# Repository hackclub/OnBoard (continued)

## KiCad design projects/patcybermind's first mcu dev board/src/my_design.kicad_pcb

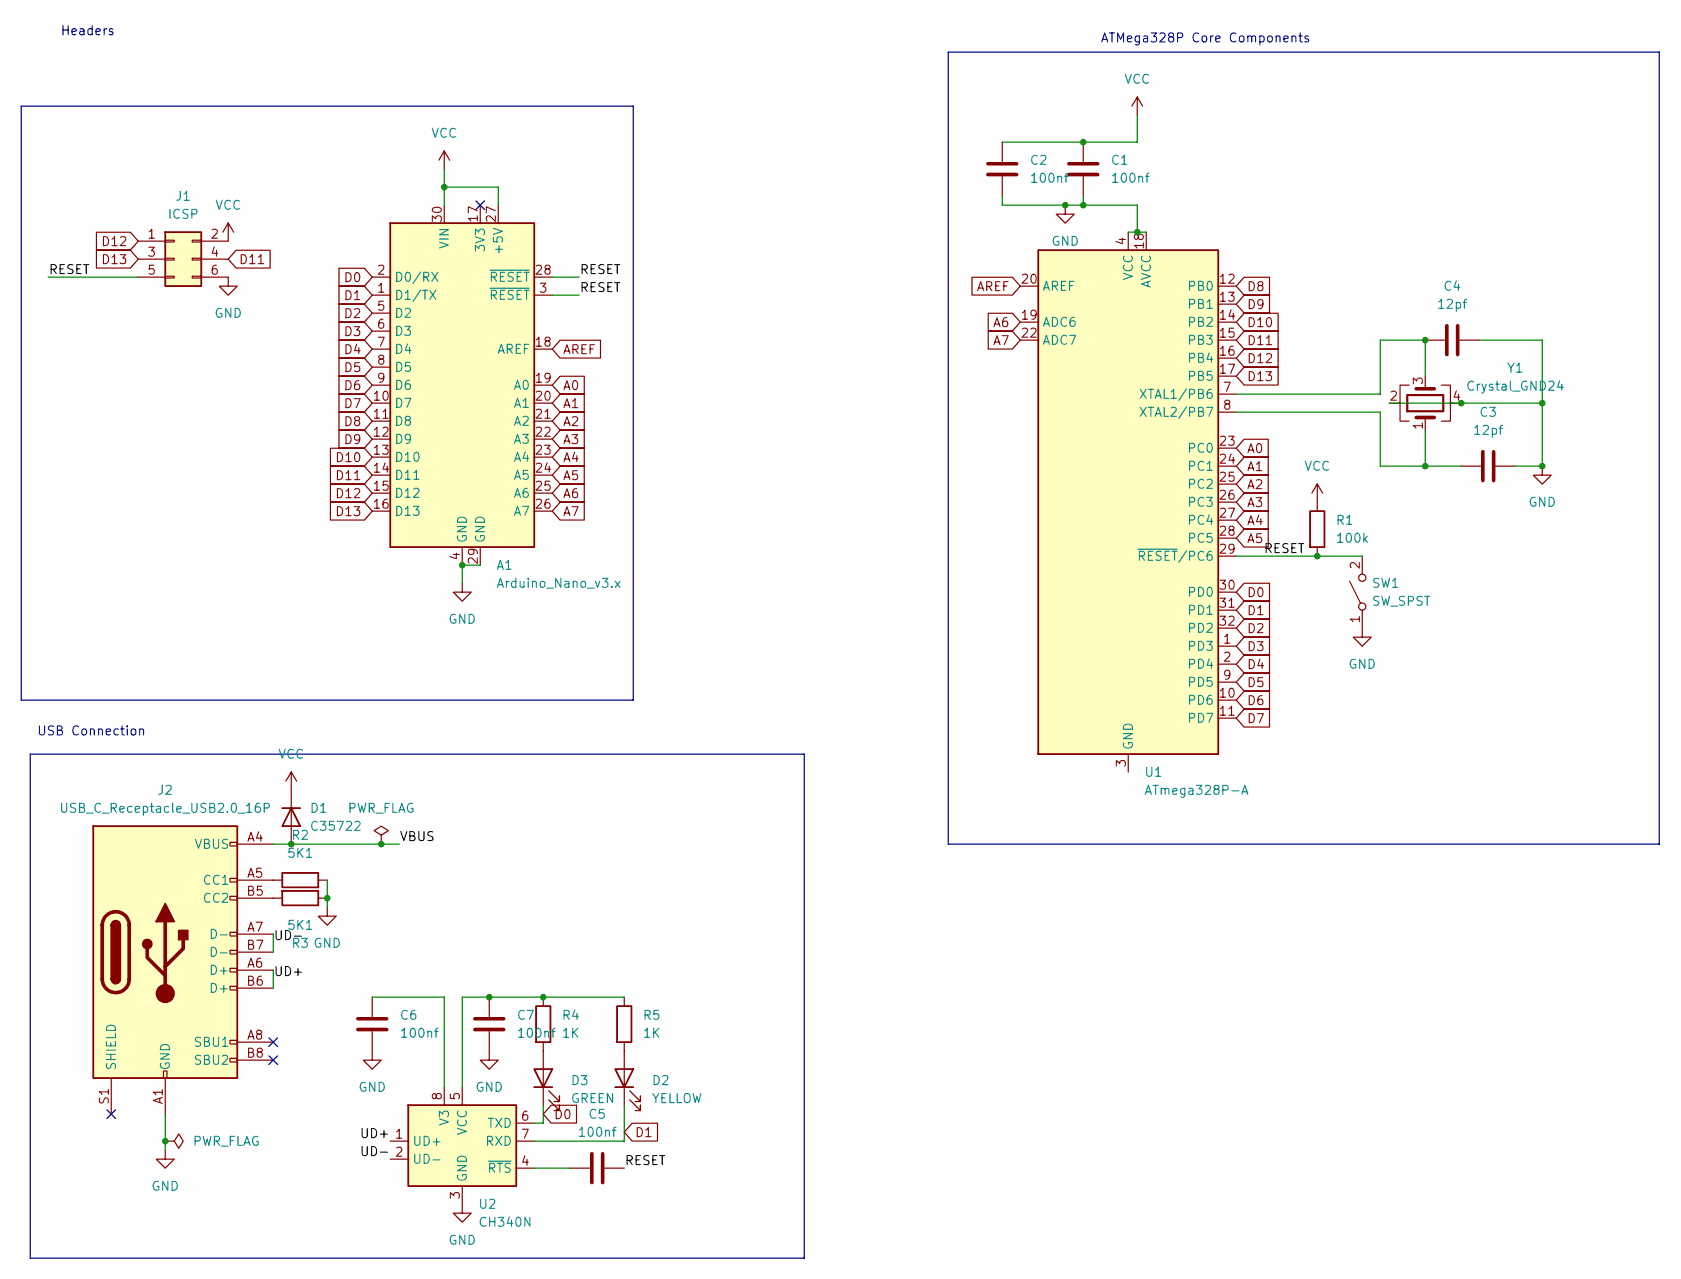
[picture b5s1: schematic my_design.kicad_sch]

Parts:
A1: Arduino_Nano_v3.x; Arduino_Nano_WithMountingHoles
C1, C2, C5, C6, C7: 100nf; C_0805_2012Metric_Pad1.18x1.45mm_HandSolder; LCSC C49678
C3, C4: 12pf; C_0805_2012Metric_Pad1.18x1.45mm_HandSolder; LCSC C1792
D1: C35722; D_SMC_Handsoldering; LCSC C35722
D2: YELLOW; LED_0805_2012Metric_Pad1.15x1.40mm_HandSolder; LCSC C2296
D3: GREEN; LED_0805_2012Metric_Pad1.15x1.40mm_HandSolder; LCSC C2297
J1: ICSP; PinHeader_2x03_P2.54mm_Vertical
J2: USB_C_Receptacle_USB2.0_16P; USB_C_Receptacle_HRO_TYPE-C-31-M-12; LCSC C2988369
R1: 100k; R_0805_2012Metric_Pad1.20x1.40mm_HandSolder; LCSC C17414
R2, R3: 5K1; R_0805_2012Metric_Pad1.20x1.40mm_HandSolder; LCSC C27834
R4, R5: 1K; R_0805_2012Metric_Pad1.20x1.40mm_HandSolder; LCSC C17513
SW1: SW_SPST; SW_Push_1P1T_XKB_TS-1187A; LCSC C318884
U1: ATmega328P-A; TQFP-32_7x7mm_P0.8mm; LCSC C14877
U2: CH340N; SOP-8_3.9x4.9mm_P1.27mm; LCSC C2977777
Y1: Crystal_GND24; Crystal_SMD_3225-4Pin_3.2x2.5mm_HandSoldering; LCSC C13738

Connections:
/RESET: A1.3 (~RESET), A1.28 (~RESET), C5.2, J1.5, R1.2, SW1.2 (B), U1.29 (~RESET/PC6)
/UD+: J2.A6 (D+), J2.B6 (D+), U2.1 (UD+)
/UD-: J2.A7 (D-), J2.B7 (D-), U2.2 (UD-)
/VBUS: D1.2 (A), J2.A4 (VBUS), J2.A9 (VBUS), J2.B4 (VBUS), J2.B9 (VBUS)
A0: A1.19 (A0), U1.23 (PC0)
A1: A1.20 (A1), U1.24 (PC1)
A2: A1.21 (A2), U1.25 (PC2)
A3: A1.22 (A3), U1.26 (PC3)
A4: A1.23 (A4), U1.27 (PC4)
A5: A1.24 (A5), U1.28 (PC5)
A6: A1.25 (A6), U1.19 (ADC6)
A7: A1.26 (A7), U1.22 (ADC7)
AREF: A1.18 (AREF), U1.20 (AREF)
D0: A1.2 (D0/RX), D3.1 (K), U1.30 (PD0), U2.6 (TXD)
D1: A1.1 (D1/TX), D2.1 (K), U1.31 (PD1), U2.7 (RXD)
D2: A1.5 (D2), U1.32 (PD2)
D3: A1.6 (D3), U1.1 (PD3)
D4: A1.7 (D4), U1.2 (PD4)
D5: A1.8 (D5), U1.9 (PD5)
D6: A1.9 (D6), U1.10 (PD6)
D7: A1.10 (D7), U1.11 (PD7)
D8: A1.11 (D8), U1.12 (PB0)
D9: A1.12 (D9), U1.13 (PB1)
D10: A1.13 (D10), U1.14 (PB2)
D11: A1.14 (D11), J1.4, U1.15 (PB3)
D12: A1.15 (D12), J1.1, U1.16 (PB4)
D13: A1.16 (D13), J1.3, U1.17 (PB5)
GND: A1.4 (GND), A1.29 (GND), C1.2, C2.1, C3.2, C4.2, C6.2, C7.2, J1.6, J2.A1 (GND), J2.A12 (GND), J2.B1 (GND), J2.B12 (GND), R2.2, R3.1, SW1.1 (A), U1.4 (VCC), U1.6 (VCC), U1.18 (AVCC), U2.3 (GND), Y1.2, Y1.4
unnamed: D2.2 (A), R5.2
unnamed: D3.2 (A), R4.2
unnamed: J2.A5 (CC1), R2.1
unnamed: J2.B5 (CC2), R3.2
unnamed: U1.3 (GND), U1.5 (GND), U1.21 (GND)
unnamed: C4.1, U1.7 (XTAL1/PB6), Y1.3
unnamed: C3.1, U1.8 (XTAL2/PB7), Y1.1
unnamed: C6.1, U2.8 (V3)
unnamed: C7.1, R4.1, R5.1, U2.5 (VCC)
unnamed: C5.1, U2.4 (~RTS)
VCC: A1.27 (+5V), A1.30 (VIN), C1.1, C2.2, D1.1 (K), J1.2, R1.1

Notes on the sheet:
ATMega328P Core Components
Headers
USB Connection

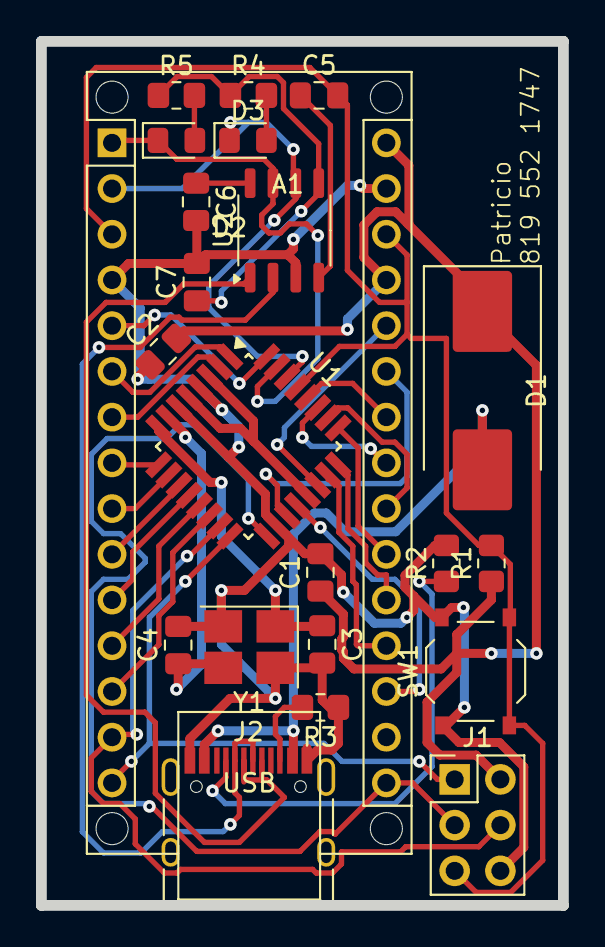
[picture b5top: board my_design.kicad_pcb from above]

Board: 2 copper layers, 29.0 x 48.0 mm, 22 parts (0 on the bottom side), 39 nets.

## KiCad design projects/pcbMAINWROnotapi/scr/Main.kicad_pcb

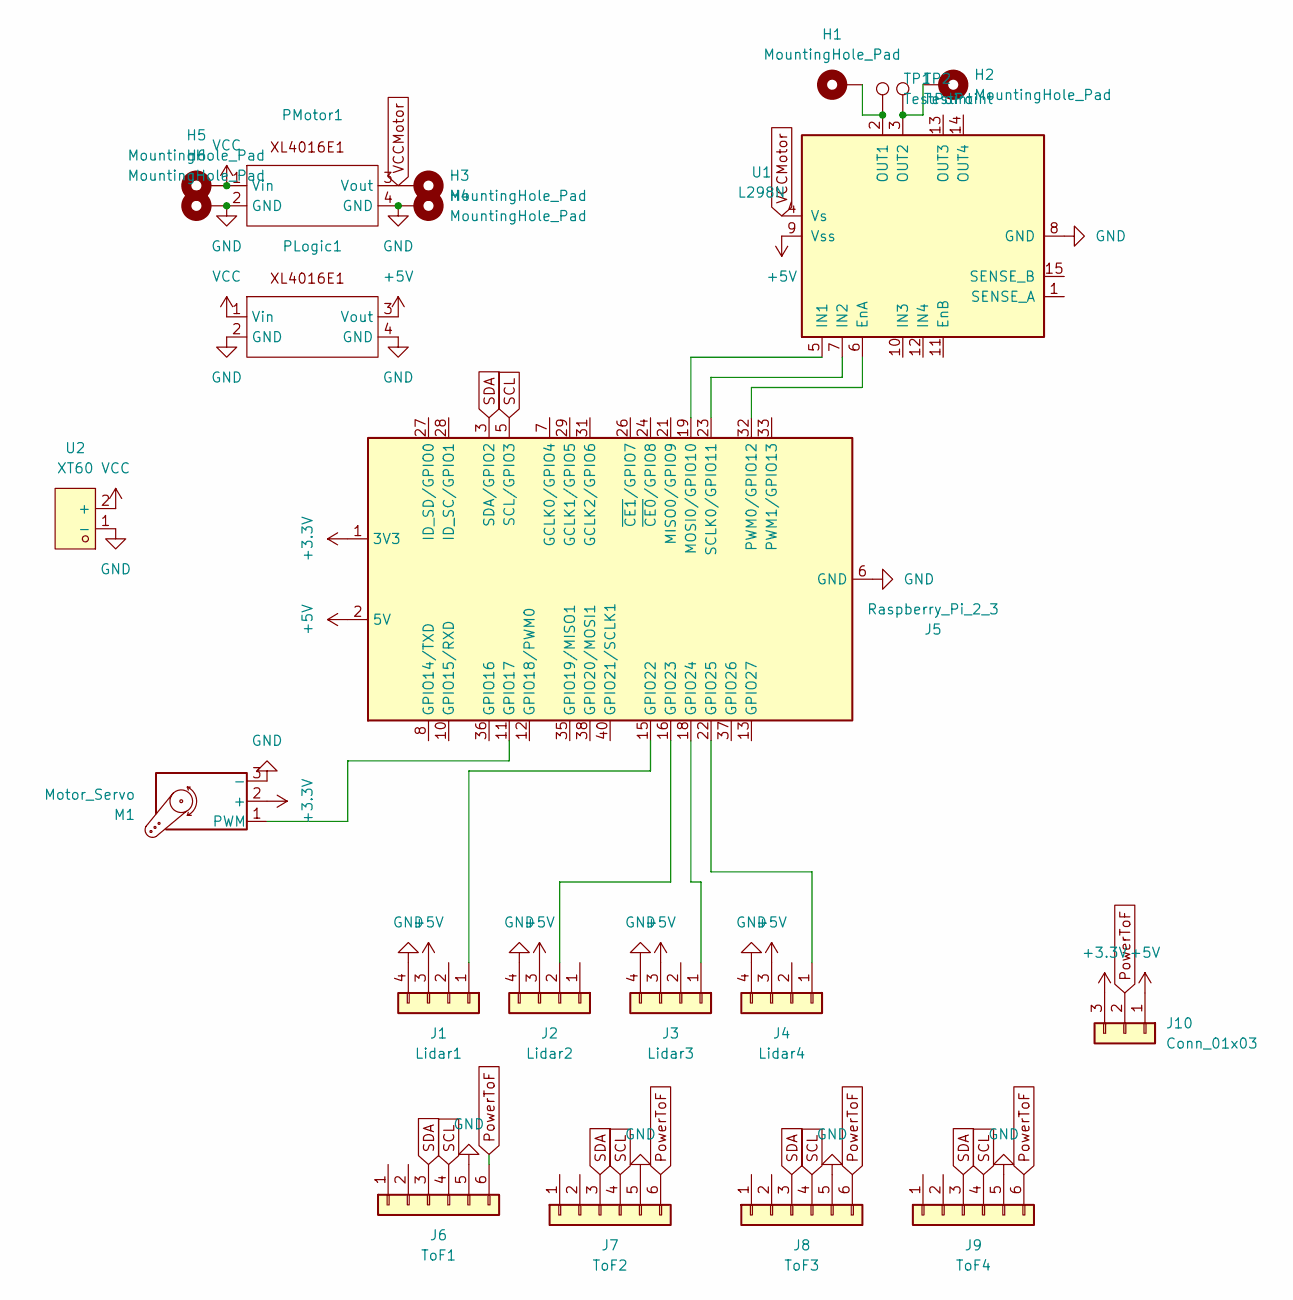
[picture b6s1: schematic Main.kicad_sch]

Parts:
H1, H2, H3, H4, H5, H6: MountingHole_Pad; MountingHole_4mm_Pad_Via
J1: Lidar1; PinHeader_1x04_P2.54mm_Vertical
J2: Lidar2; PinHeader_1x04_P2.54mm_Vertical
J3: Lidar3; PinHeader_1x04_P2.54mm_Vertical
J4: Lidar4; PinHeader_1x04_P2.54mm_Vertical
J5: Raspberry_Pi_2_3; PinSocket_2x20_P2.54mm_Vertical
J6: ToF1; PinSocket_1x06_P2.54mm_Horizontal
J7: ToF2; PinSocket_1x06_P2.54mm_Horizontal
J8: ToF3; PinSocket_1x06_P2.54mm_Horizontal
J9: ToF4; PinSocket_1x06_P2.54mm_Horizontal
J10: Conn_01x03; PinHeader_1x03_P2.54mm_Vertical
M1: Motor_Servo; PinHeader_1x03_P2.54mm_Vertical
PLogic1: PinHeader_1x04_P2.54mm_Vertical
PMotor1: PinHeader_1x04_P2.54mm_Vertical
TP1, TP2: TestPoint
U1: L298N; TO-220-15_P2.54x2.54mm_StaggerOdd_Lead4.58mm_Vertical
U2: XT60; CONN-TH_XT60; LCSC Part C98733

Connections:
+3.3V: J5.1 (3V3), J5.17 (3V3), J10.3, M1.2 (+)
+5V: J1.3, J2.3, J3.3, J4.3, J5.2 (5V), J5.4 (5V), J10.1, PLogic1.3 (Vout), U1.9 (Vss)
GND: H4.1, H6.1, J1.4, J2.4, J3.4, J4.4, J5.6 (GND), J5.9 (GND), J5.14 (GND), J5.20 (GND), J5.25 (GND), J5.30 (GND), J5.34 (GND), J5.39 (GND), J6.5, J7.5, J8.5, J9.5, M1.3 (-), PLogic1.2 (GND), PLogic1.4 (GND), PMotor1.2 (GND), PMotor1.4 (GND), U1.8 (GND), U2.1 (-)
unnamed: J1.1, J5.15 (GPIO22)
unnamed: J2.2, J5.16 (GPIO23)
unnamed: J3.1, J5.18 (GPIO24)
unnamed: J4.1, J5.22 (GPIO25)
unnamed: J5.11 (GPIO17), M1.1 (PWM)
unnamed: J5.19 (MOSI0/GPIO10), U1.5 (IN1)
unnamed: J5.32 (PWM0/GPIO12), U1.6 (EnA)
unnamed: J5.23 (SCLK0/GPIO11), U1.7 (IN2)
unnamed: H1.1, TP1.1, U1.2 (OUT1)
unnamed: H2.1, TP2.1, U1.3 (OUT2)
PowerToF: J6.6, J7.6, J8.6, J9.6, J10.2
SCL: J5.5 (SCL/GPIO3), J6.4, J7.4, J8.4, J9.4
SDA: J5.3 (SDA/GPIO2), J6.3, J7.3, J8.3, J9.3
VCC: H5.1, PLogic1.1 (Vin), PMotor1.1 (Vin), U2.2 (+)
VCCMotor: H3.1, PMotor1.3 (Vout), U1.4 (Vs)

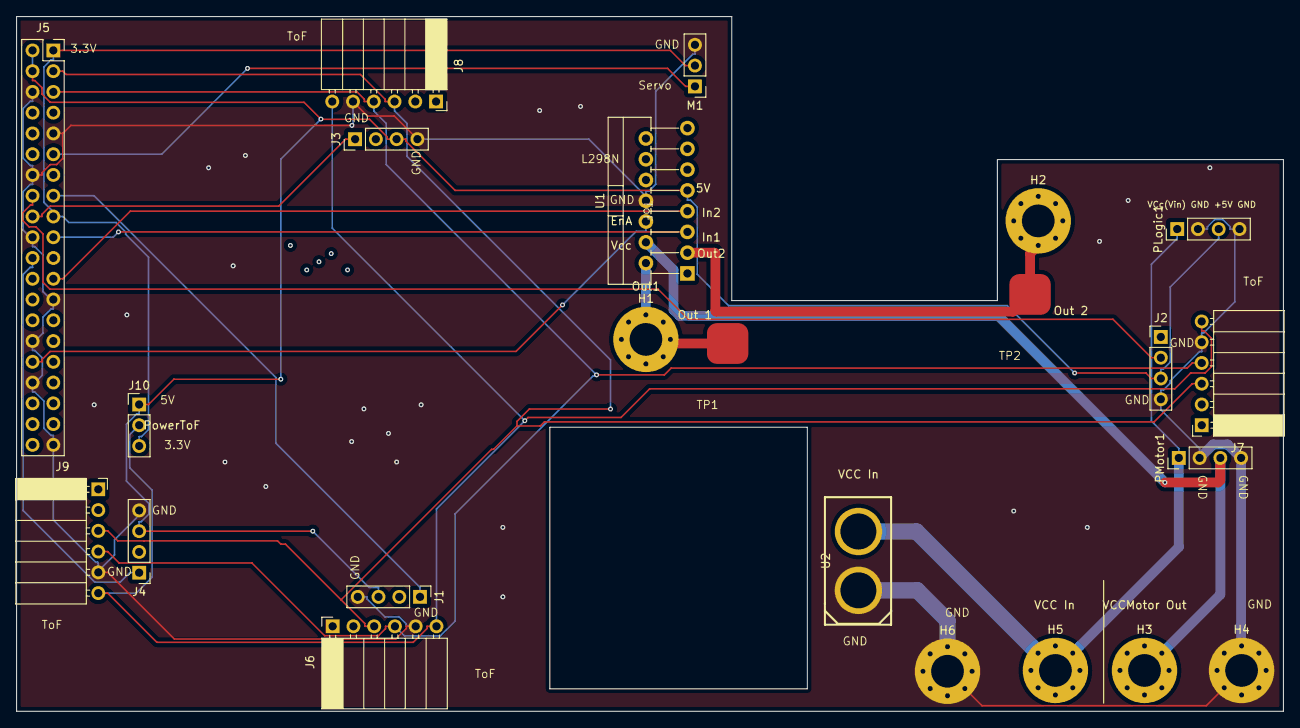
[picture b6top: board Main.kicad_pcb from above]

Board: 2 copper layers, 155.0 x 85.0 mm, 23 parts (0 on the bottom side), 18 nets.

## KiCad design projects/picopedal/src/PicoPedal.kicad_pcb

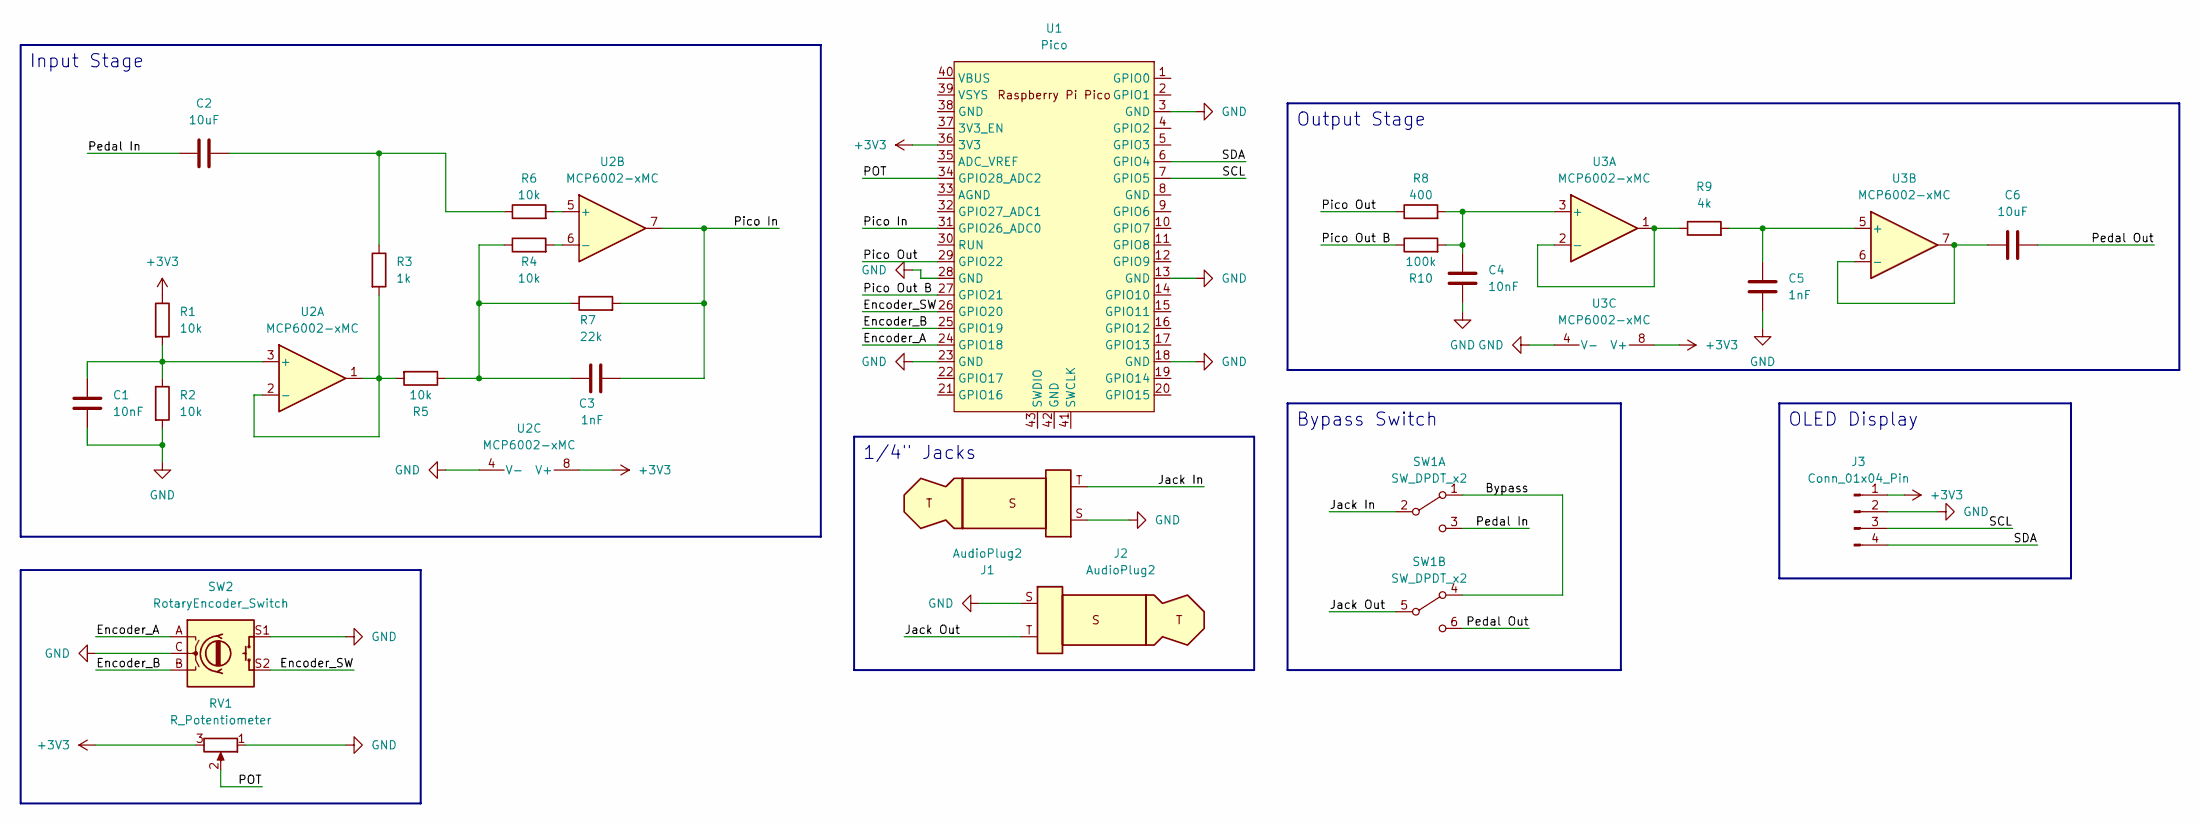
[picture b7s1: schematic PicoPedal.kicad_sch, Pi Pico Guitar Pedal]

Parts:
C1, C4: 10nF; C_Disc_D5.0mm_W2.5mm_P5.00mm
C2, C6: 10uF; CP_Radial_D5.0mm_P2.50mm
C3, C5: 1nF; C_Disc_D5.0mm_W2.5mm_P5.00mm
J1, J2: AudioPlug2; Jack_6.35mm_Neutrik_NMJ6HFD2_Horizontal
J3: Conn_01x04_Pin; PinHeader_1x04_P2.54mm_Vertical
R1, R2, R4, R5, R6: 10k; R_Axial_DIN0207_L6.3mm_D2.5mm_P10.16mm_Horizontal
R3: 1k; R_Axial_DIN0207_L6.3mm_D2.5mm_P10.16mm_Horizontal
R7: 22k; R_Axial_DIN0207_L6.3mm_D2.5mm_P10.16mm_Horizontal
R8: 400; R_Axial_DIN0207_L6.3mm_D2.5mm_P10.16mm_Horizontal
R9: 4k; R_Axial_DIN0207_L6.3mm_D2.5mm_P10.16mm_Horizontal
R10: 100k; R_Axial_DIN0207_L6.3mm_D2.5mm_P10.16mm_Horizontal
RV1: R_Potentiometer; Potentiometer_Alps_RK09L_Single_Vertical
SW1: SW_DPDT_x2; SW_PUSH_E-Switch_FS5700DP_DPDT
SW2: RotaryEncoder_Switch; RotaryEncoder_Alps_EC11E-Switch_Vertical_H20mm
U1: Pico; RPi_Pico_SMD_TH
U2, U3: MCP6002-xMC; DIP-8_W7.62mm_Socket

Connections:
+3V3: J3.1, R1.1, RV1.3, U1.36 (3V3), U2.8 (V+), U3.8 (V+)
/Bypass: SW1.1 (A), SW1.4 (A)
/Encoder_A: SW2.A, U1.24 (GPIO18)
/Encoder_B: SW2.B, U1.25 (GPIO19)
/Encoder_SW: SW2.S2, U1.26 (GPIO20)
/Jack In: J1.T, SW1.2 (B)
/Jack Out: J2.T, SW1.5 (B)
/POT: RV1.2, U1.34 (GPIO28_ADC2)
/Pedal In: C2.2, SW1.3 (C)
/Pedal Out: C6.1, SW1.6 (C)
/Pico In: C3.2, R7.2, U1.31 (GPIO26_ADC0), U2.7
/Pico Out: R8.1, U1.29 (GPIO22)
/Pico Out B: R10.1, U1.27 (GPIO21)
/SCL: J3.3, U1.7 (GPIO5)
/SDA: J3.4, U1.6 (GPIO4)
GND: C1.2, C4.1, C5.1, J1.S, J2.S, J3.2, R2.2, RV1.1, SW2.C, SW2.S1, U1.3 (GND), U1.13 (GND), U1.18 (GND), U1.23 (GND), U1.28 (GND), U2.4 (V-), U3.4 (V-)
unnamed: C2.1, R3.1, R6.1
unnamed: C3.1, R4.1, R5.1, R7.1
unnamed: C1.1, R1.2, R2.1, U2.3 (+)
unnamed: R3.2, R5.2, U2.1, U2.2 (-)
unnamed: R6.2, U2.5 (+)
unnamed: R4.2, U2.6 (-)
unnamed: C4.2, R8.2, R10.2, U3.3 (+)
unnamed: R9.1, U3.1, U3.2 (-)
unnamed: C5.2, R9.2, U3.5 (+)
unnamed: C6.2, U3.6 (-), U3.7

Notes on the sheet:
Bypass Switch
Input Stage
Output Stage
1/4" Jacks
OLED Display

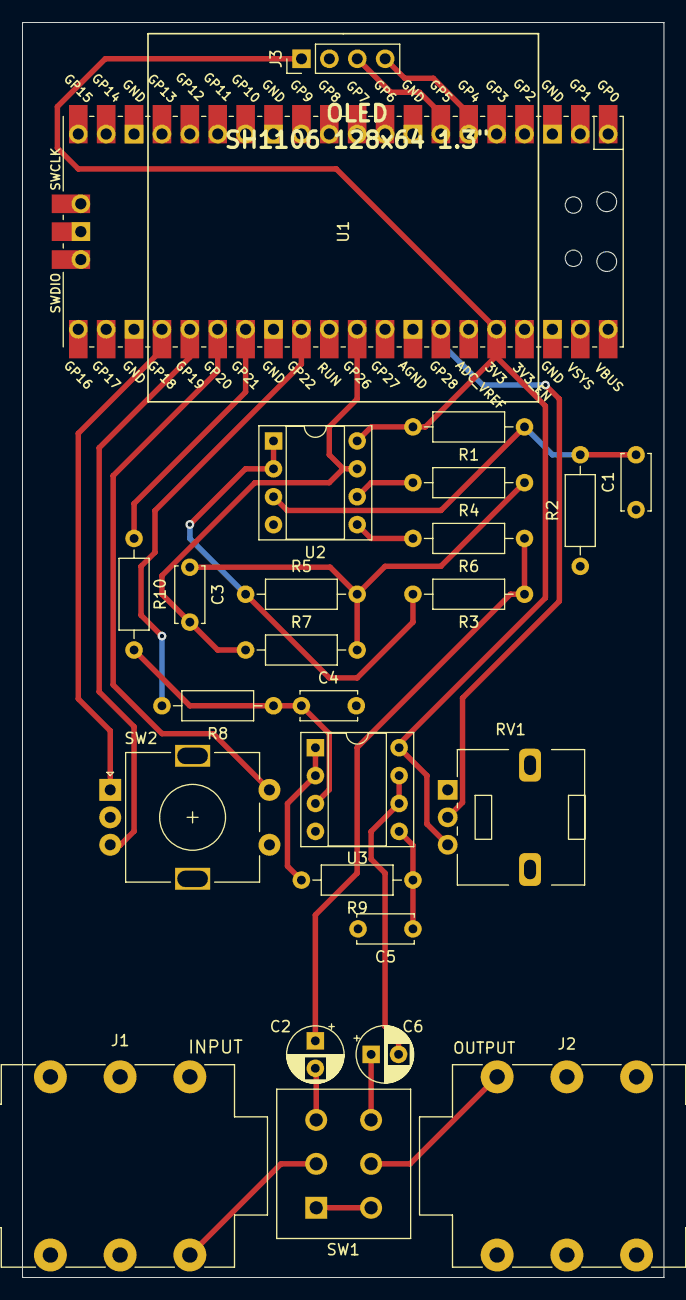
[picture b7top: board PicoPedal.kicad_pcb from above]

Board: 2 copper layers, 58.4 x 114.3 mm, 25 parts (0 on the bottom side), 26 nets.

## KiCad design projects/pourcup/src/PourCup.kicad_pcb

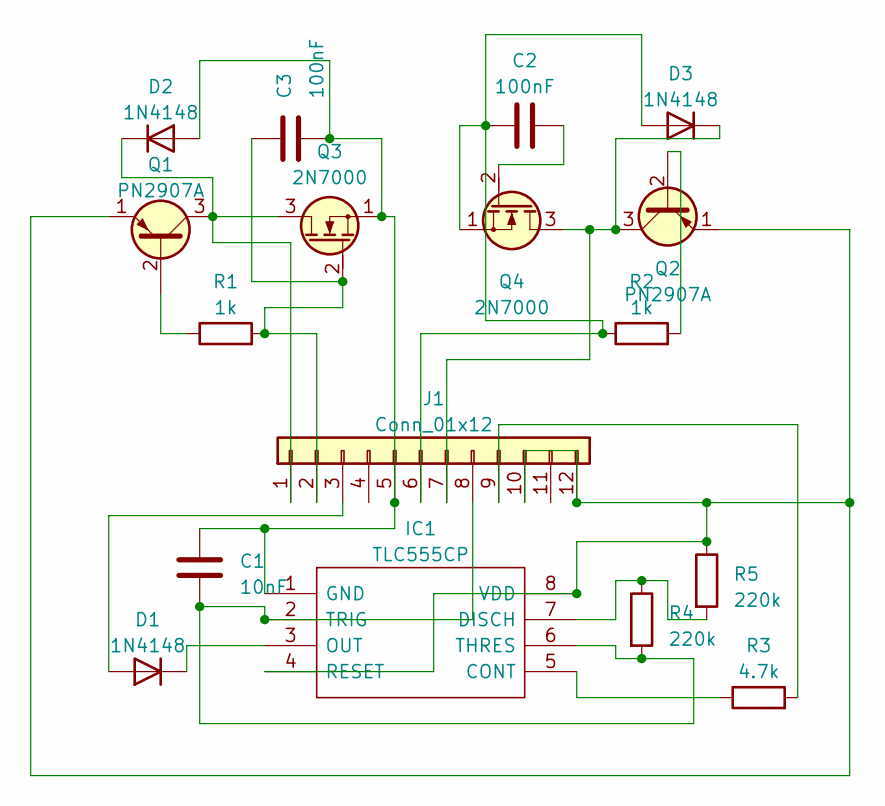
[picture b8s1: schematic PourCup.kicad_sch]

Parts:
C1: 10nF; C_Disc_D4.7mm_W2.5mm_P5.00mm
C2, C3: 100nF; C_Disc_D5.0mm_W2.5mm_P5.00mm
D1, D2, D3: 1N4148; D_DO-35_SOD27_P7.62mm_Horizontal
IC1: TLC555CP; DIP794W53P254L959H508Q8N; Mouser Part Number 595-TLC555CP
J1: Conn_01x12; PinHeader_1x12_P2.54mm_Vertical
Q1, Q2: PN2907A; TO-92-3L_5P33X5P2_ONS
Q3, Q4: 2N7000; TO_7000_VIS
R1, R2: 1k; R_Axial_DIN0204_L3.6mm_D1.6mm_P7.62mm_Horizontal
R3: 4.7k; R_Axial_DIN0204_L3.6mm_D1.6mm_P7.62mm_Horizontal
R4, R5: 220k; R_Axial_DIN0207_L6.3mm_D2.5mm_P7.62mm_Horizontal

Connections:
unnamed: D1.2 (A), J1.3
unnamed: D1.1 (K), IC1.3 (OUT)
unnamed: C1.1, C3.2, D2.2 (A), IC1.1 (GND), J1.5, Q3.1 (S)
unnamed: D2.1 (K), J1.1, Q1.3 (C), Q3.3 (D)
unnamed: C2.1, D3.2 (A), J1.6, Q4.1 (S), R2.1
unnamed: D3.1 (K), J1.7, Q2.3 (C), Q4.3 (D)
unnamed: IC1.5 (CONT), R3.1
unnamed: IC1.7 (DISCH), R4.1, R5.2
unnamed: IC1.4 (RESET), IC1.8 (VDD), J1.10, J1.12, Q1.1 (E), Q2.1 (E), R5.1
unnamed: C1.2, IC1.2 (TRIG), IC1.6 (THRES), J1.8, R4.2
unnamed: C3.1, J1.2, Q3.2 (G), R1.2
unnamed: J1.9, R3.2
unnamed: Q1.2 (B), R1.1
unnamed: Q2.2 (B), R2.2
unnamed: C2.2, Q4.2 (G)

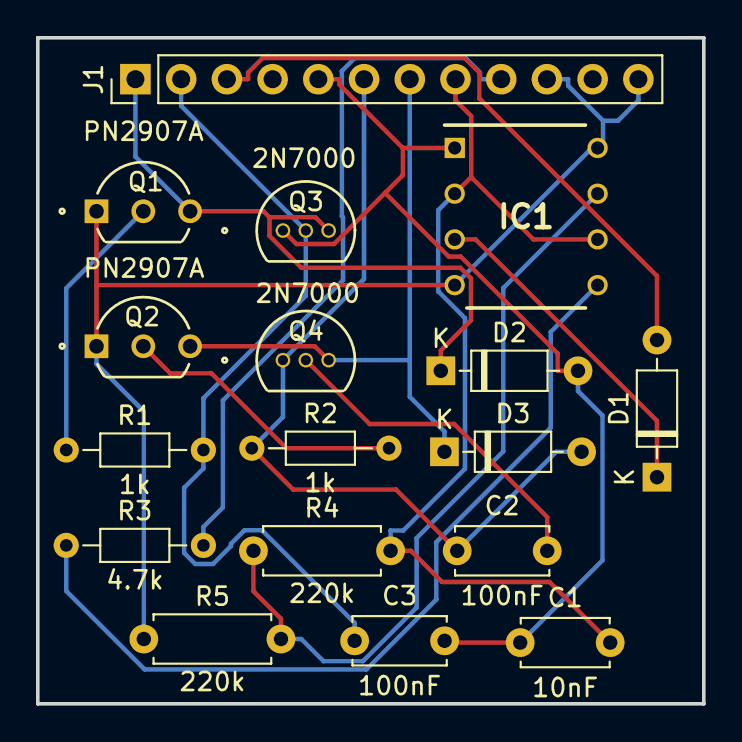
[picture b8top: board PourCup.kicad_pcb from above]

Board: 2 copper layers, 37.0 x 37.0 mm, 17 parts (0 on the bottom side), 15 nets.
